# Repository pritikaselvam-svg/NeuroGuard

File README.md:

# NeuroGuard[README.md](https://github.com/user-attachments/files/31235367/README.md)
# NeuroGuard --- Wearable Alzheimer's Patient Monitoring & Caregiver Support System

NeuroGuard is an interdisciplinary engineering prototype combining
**biological/behavioral reasoning, embedded electronics, PCB design,
software, Android packaging, and wearable CAD**.
## PCB Design

> **Current prototype status:** The caregiver application is functional
> in Demo/Simulation Mode. The Android application is a WebView wrapper
> around the HTML/CSS/JavaScript interface. The physical PCB and live
> sensor-to-phone BLE pipeline remain hardware-integration stages.

## What the system is designed to support

-   Heart-rate monitoring using MAX30102.
-   SpO2-related optical measurement capability.
-   Motion/activity monitoring using MPU6050.
-   Fall-event detection logic.
-   Unusual activity / wandering-support logic.
-   Sleep/activity trend estimation.
-   Medication reminders and adherence logging.
-   Haptic alerts through a vibration motor.
-   Battery monitoring.
-   Caregiver dashboard and alerts.

## System architecture

``` text
       BIOLOGICAL / BEHAVIORAL LAYER
                    |
                    v
             Signal selection
                    |
                    v
 MAX30102 ----+                 +---- MPU6050
              |                 |
              +---- ESP32-C3 ---+
                       |
             +---------+---------+
             |         |         |
             v         v         v
          Haptic    Battery     BLE
          Alert     Monitor      |
                                 v
                           Android App
                                 |
                                 v
                          Caregiver UI
```

## Repository structure

``` text
docs/        Research, design decisions, testing and evidence
hardware/    KiCad, Gerbers, BOM and datasheets
firmware/    ESP32-C3 firmware
app/         Web application and Android wrapper
cad/         Wearable enclosure files
data/        Simulated/test data
media/       Portfolio images and diagrams
```

## Important medical boundary

NeuroGuard is a **student engineering prototype, not a medical
diagnostic device**.

The current system must not be described as diagnosing Alzheimer's
disease, infection, dehydration, or another medical condition. In
particular, MAX30102 heart-rate data is a physiological signal, not an
infection detector. The current hardware also does not contain a
dedicated temperature sensor.

## Current versus future implementation

### Current

``` text
Simulated JavaScript data
        ↓
HTML/CSS/JS dashboard
        ↓
Android WebView
```

### Target

``` text
MAX30102 + MPU6050 + battery
             ↓
          ESP32-C3
             ↓
             BLE
             ↓
        Android App
             ↓
       Caregiver UI
```

## Engineering evidence

The repository documents the complete path:

**Problem → research → biological mapping → requirements → component
selection → schematic → PCB → firmware architecture → app → CAD →
testing → limitations → future work.**

## Status

-   [x] Problem definition
-   [x] Biological/behavioral mapping
-   [x] Component selection
-   [x] KiCad schematic
-   [x] PCB routing
-   [x] Web dashboard
-   [x] Simulated sensor layer
-   [x] Android WebView packaging
-   [ ] Physical PCB bring-up
-   [ ] Real sensor validation
-   [ ] ESP32-C3 firmware validation
-   [ ] BLE integration
-   [ ] Enclosure fabrication
-   [ ] Integrated hardware testing
-   [ ] Human/clinical validation

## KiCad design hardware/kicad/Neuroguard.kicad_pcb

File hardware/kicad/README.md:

# KiCad Design Files

This folder contains the editable KiCad design files for the NeuroGuard wearable PCB.

## Files

- `NeuroGuard.kicad_sch` — Complete circuit schematic
- `NeuroGuard.kicad_pcb` — PCB layout and routing
- `NeuroGuard.kicad_pro` — KiCad project configuration

## Design

The PCB integrates:

- WEMOS C3 Mini / ESP32-C3
- MAX30102 physiological sensor
- MPU6050 motion sensor
- TP4056 battery charging
- 3.3 V regulation
- Battery voltage monitoring
- Vibration motor driver
- Status LED
- USB-C power input

## Design Verification

The schematic was checked using KiCad Electrical Rules Check (ERC).

The PCB was subsequently routed and checked using KiCad Design Rules Check (DRC).

## Editing

Open the `.kicad_pro` file in KiCad to access the complete project.

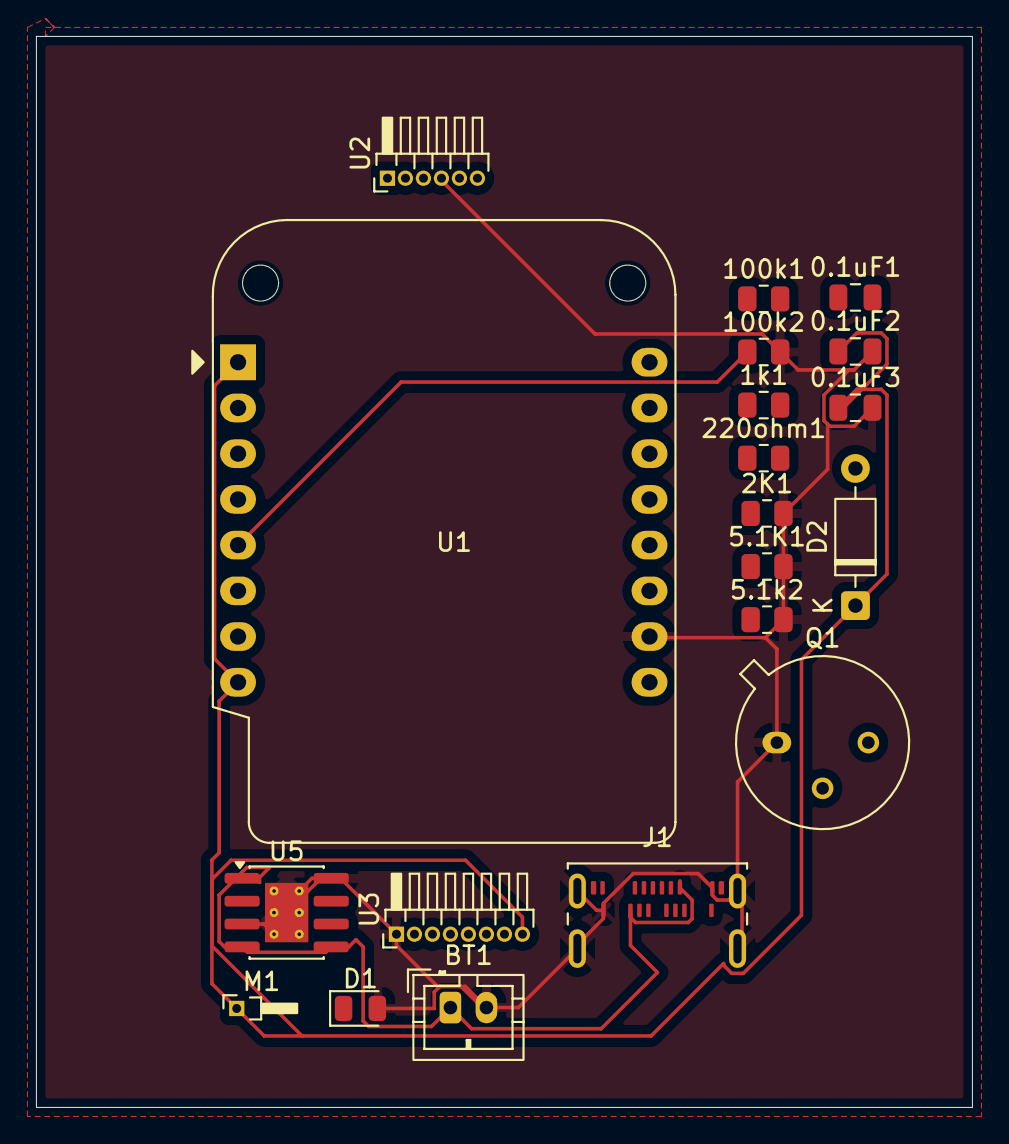
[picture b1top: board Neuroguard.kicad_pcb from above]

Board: 2 copper layers, 52.0 x 59.5 mm, 20 parts (0 on the bottom side), 4 nets.

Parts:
0.1uF1, 0.1uF2, 0.1uF3: C; C_0805_2012Metric
1k1, 2K1, 5.1K1, 5.1k2, 100k1, 100k2, 220ohm1: R; R_0805_2012Metric
BT1: Battery; JST_PH_B2B-PH-K_1x02_P2.00mm_Vertical
D1: LED; LED_0805_2012Metric
D2: 1N4148; D_DO-35_SOD27_P7.62mm_Horizontal
J1: USB_C_Receptacle_PowerOnly_6P; USB_C_Receptacle_Amphenol_124019772112A
M1: Motor_DC; PinHeader_1x01_P1.00mm_Horizontal
Q1: 2N2219; TO-39-3
U1: WEMOS_C3_mini
U2: MAX30102; PinHeader_1x06_P1.00mm_Horizontal
U3: MPU-6050; PinHeader_1x08_P1.00mm_Horizontal
U5: TP4056-42-ESOP8; SOIC-8-1EP_3.9x4.9mm_P1.27mm_EP2.41x3.3mm_ThermalVias

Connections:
GND: 0.1uF2.2, 0.1uF3.2, 2K1.2, 5.1K1.2, 5.1k2.2, 100k2.2, BT1.2 (-), D1.2 (A), J1.A12 (GND), J1.B12 (GND), J1.S1 (SHIELD), Q1.1 (E), U1.10 (GND), U2.4 (PGND), U3.1 (CLKIN), U5.3 (GND), U5.8 (CE), U5.9 (EPAD)
unnamed: BT1.1 (+), J1.A9 (VBUS), J1.B9 (VBUS), U5.1 (TEMP), U5.4 (V_{CC}), U5.5 (BAT)
unnamed: 0.1uF2.1, 0.1uF3.1, D2.1 (K), M1.1 (+), U1.1 (EN), U1.8 (3V3), U3.8 (VLOGIC)
unnamed: 100k2.1, U1.5 (D0)
